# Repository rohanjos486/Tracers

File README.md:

# Tracers
STM32F401RE Evaluation Board

2-layer STM32F401RE development/evaluation board designed in KiCad.

Current progress includes schematic, PCB layout, USB-C interface, 3.3V regulation, SWD, UART, SPI, I²C, GPIO expansion, user LED/button, reset circuit and ERC validation.

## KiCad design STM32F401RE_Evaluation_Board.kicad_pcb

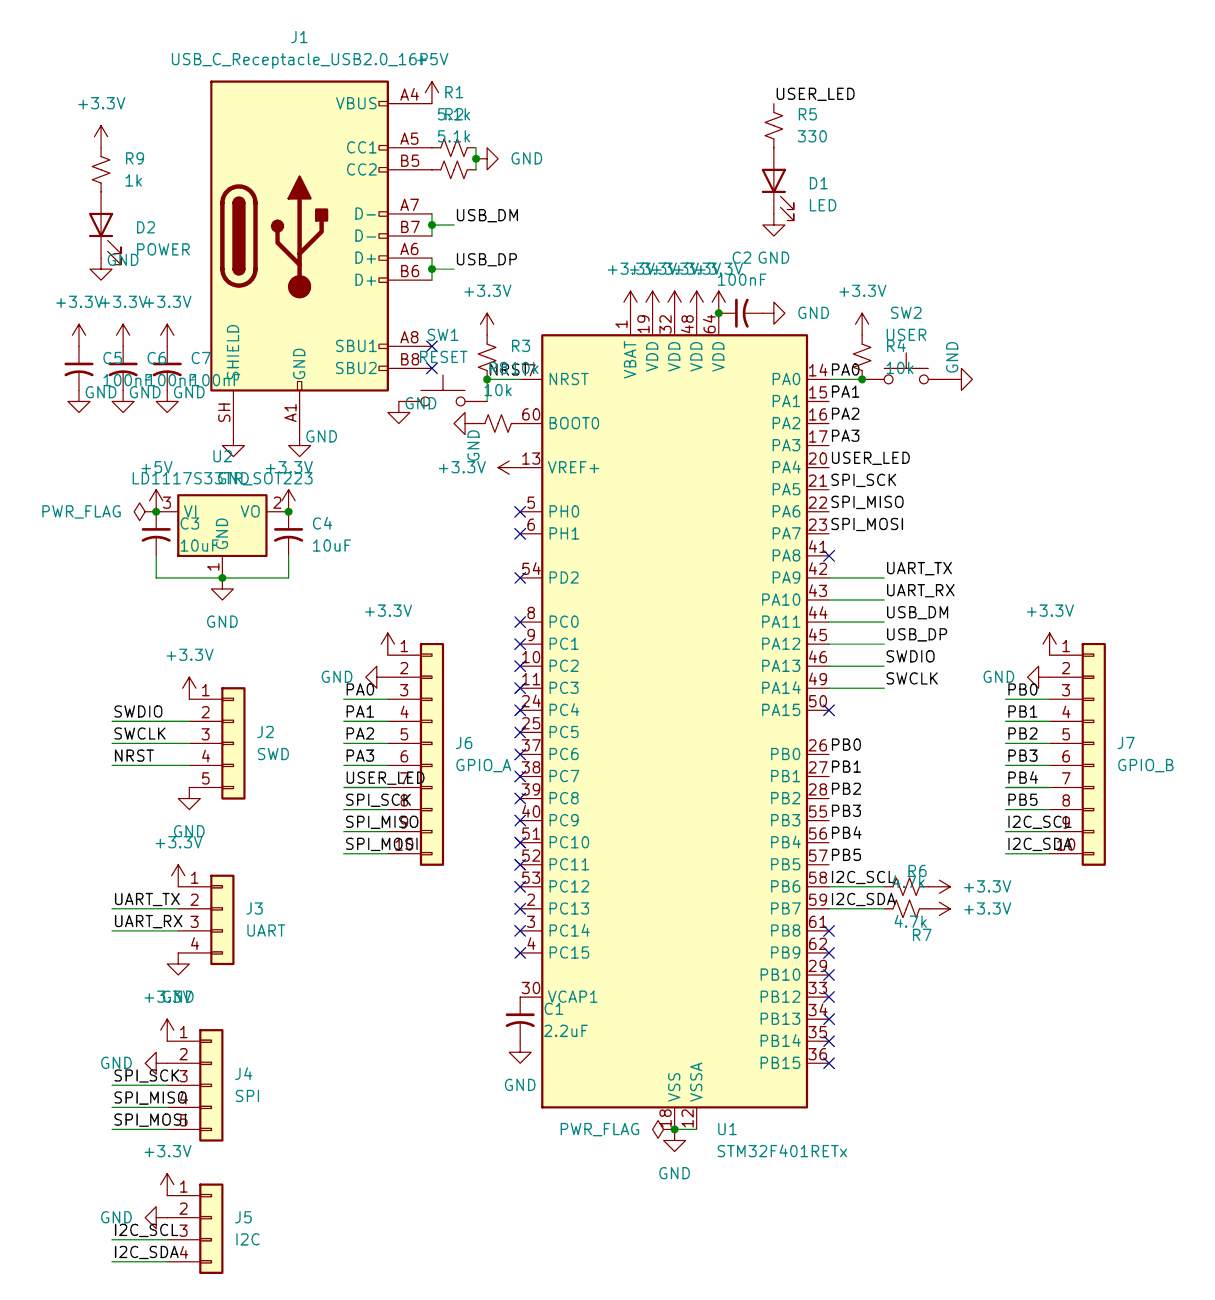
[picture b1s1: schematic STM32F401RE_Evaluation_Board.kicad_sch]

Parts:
C1: 2.2uF; C_0805_2012Metric
C2, C5, C6, C7: 100nF; C_0603_1608Metric
C3, C4: 10uF; C_0805_2012Metric
D1: LED; LED_0603_1608Metric
D2: POWER; LED_0603_1608Metric
J1: USB_C_Receptacle_USB2.0_16P; USB_C_Receptacle_GCT_USB4105-xx-A_16P_TopMnt_Horizontal
J2: SWD; PinHeader_1x05_P2.54mm_Vertical
J3: UART; FanPinHeader_1x04_P2.54mm_Vertical
J4: SPI; PinHeader_1x05_P2.54mm_Vertical
J5: I2C; FanPinHeader_1x04_P2.54mm_Vertical
J6: GPIO_A; PinHeader_1x10_P2.54mm_Vertical
J7: GPIO_B; PinHeader_1x10_P2.54mm_Vertical
R1, R2: 5.1k; R_0603_1608Metric
R3, R4, R8: 10k; R_0603_1608Metric
R5: 330; R_0603_1608Metric
R6, R7: 4.7k; R_0603_1608Metric
R9: 1k; R_0603_1608Metric
SW1: RESET; SW_Push_1P1T-SH_NO_CK_KMR2xxG
SW2: USER; SW_Push_1P1T-SH_NO_CK_KMR2xxG
U1: STM32F401RETx; LQFP-64_10x10mm_P0.5mm
U2: LD1117S33TR_SOT223; SOT-223-3_TabPin2

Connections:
+3.3V: C2.1, C4.1, C5.1, C6.1, C7.1, J2.1, J3.1, J4.1, J5.1, J6.1, J7.1, R3.1, R4.1, R6.2, R7.2, R9.2, U1.1 (VBAT), U1.13 (VREF+), U1.19 (VDD), U1.32 (VDD), U1.48 (VDD), U1.64 (VDD), U2.2 (VO)
+5V: C3.1, J1.A4 (VBUS), J1.A9 (VBUS), J1.B4 (VBUS), J1.B9 (VBUS), U2.3 (VI)
/I2C_SCL: J5.3, J7.9, R6.1, U1.58 (PB6)
/I2C_SDA: J5.4, J7.10, R7.1, U1.59 (PB7)
/NRST: J2.4, R3.2, SW1.2, U1.7 (NRST)
/PA0: J6.3, R4.2, SW2.1, U1.14 (PA0)
/PA1: J6.4, U1.15 (PA1)
/PA2: J6.5, U1.16 (PA2)
/PA3: J6.6, U1.17 (PA3)
/PB0: J7.3, U1.26 (PB0)
/PB1: J7.4, U1.27 (PB1)
/PB2: J7.5, U1.28 (PB2)
/PB3: J7.6, U1.55 (PB3)
/PB4: J7.7, U1.56 (PB4)
/PB5: J7.8, U1.57 (PB5)
/SPI_MISO: J4.4, J6.9, U1.22 (PA6)
/SPI_MOSI: J4.5, J6.10, U1.23 (PA7)
/SPI_SCK: J4.3, J6.8, U1.21 (PA5)
/SWCLK: J2.3, U1.49 (PA14)
/SWDIO: J2.2, U1.46 (PA13)
/UART_RX: J3.3, U1.43 (PA10)
/UART_TX: J3.2, U1.42 (PA9)
/USB_DM: J1.A7 (D-), J1.B7 (D-), U1.44 (PA11)
/USB_DP: J1.A6 (D+), J1.B6 (D+), U1.45 (PA12)
/USER_LED: J6.7, R5.1, U1.20 (PA4)
GND: C1.2, C2.2, C3.2, C4.2, C5.2, C6.2, C7.2, D1.1 (K), D2.1 (K), J1.A1 (GND), J1.A12 (GND), J1.B1 (GND), J1.B12 (GND), J1.SH (SHIELD), J2.5, J3.4, J4.2, J5.2, J6.2, J7.2, R1.2, R2.2, R8.1, SW1.1, SW2.2, U1.12 (VSSA), U1.18 (VSS), U1.31 (VSS), U1.47 (VSS), U1.63 (VSS), U2.1 (GND)
unnamed: D1.2 (A), R5.2
unnamed: D2.2 (A), R9.1
unnamed: J1.A5 (CC1), R1.1
unnamed: J1.B5 (CC2), R2.1
unnamed: R8.2, U1.60 (BOOT0)
unnamed: C1.1, U1.30 (VCAP1)

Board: 2 copper layers, 29 parts (0 on the bottom side), 32 nets, no tracks yet.
